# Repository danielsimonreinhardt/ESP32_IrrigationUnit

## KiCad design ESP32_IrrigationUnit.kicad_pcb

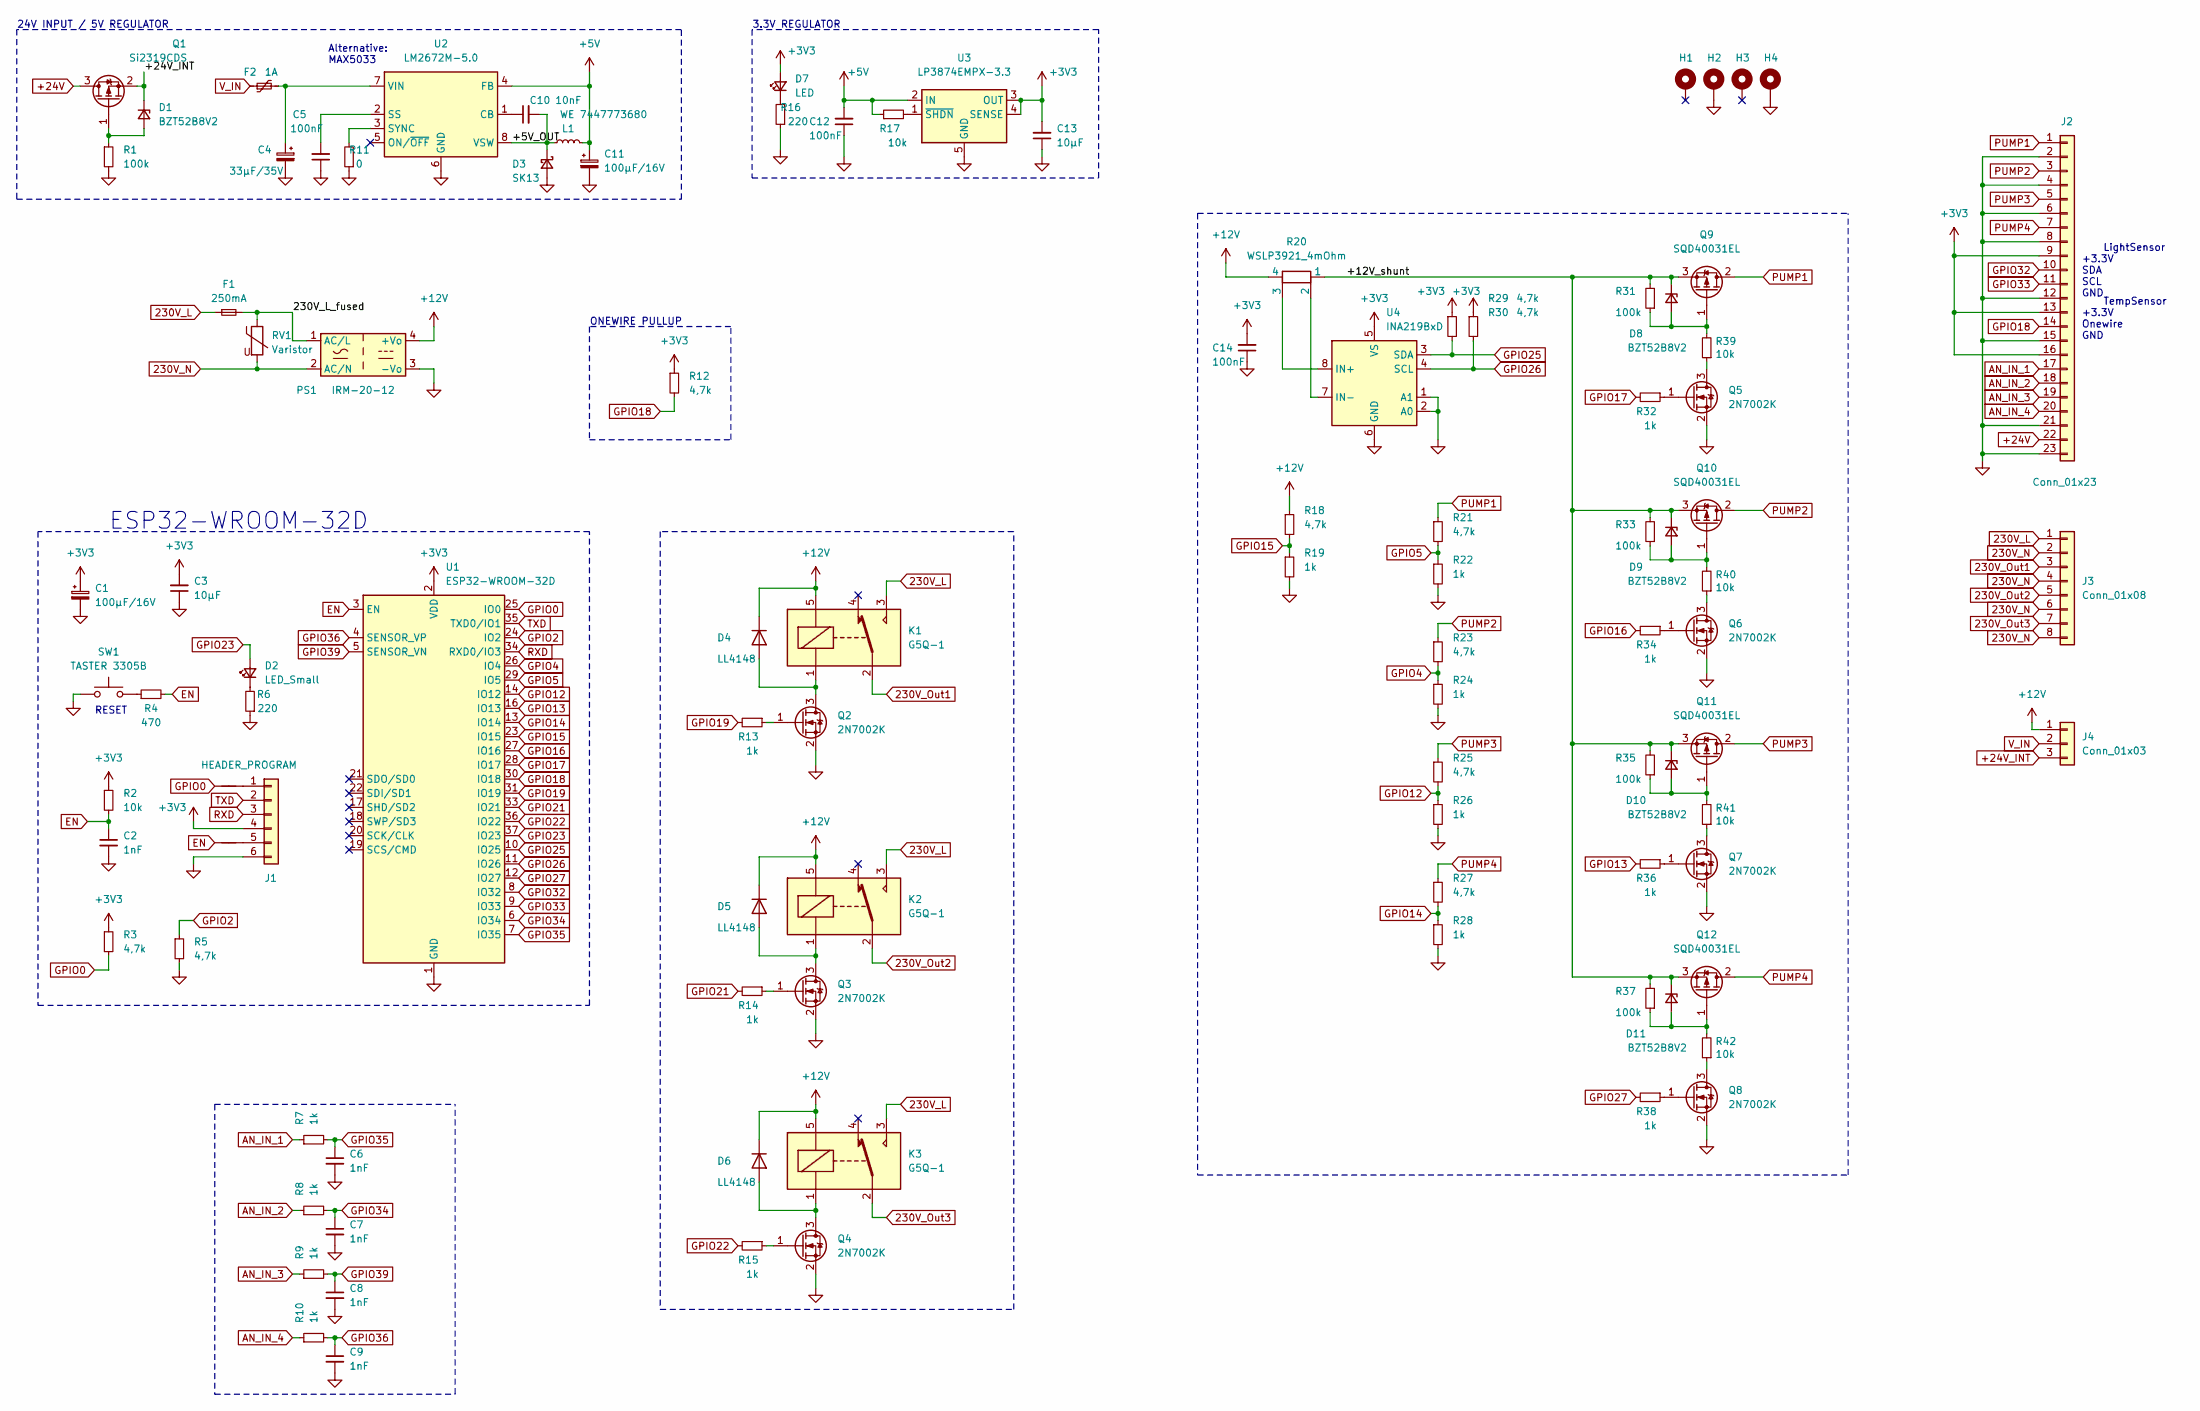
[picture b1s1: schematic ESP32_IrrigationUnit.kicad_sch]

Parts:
C1, C11: 100µF/16V; CP_Elec_6.3x5.8
C2, C6, C7, C8, C9: 1nF; C_0603_1608Metric
C3, C13: 10µF; C_0805_2012Metric
C4: 33µF/35V; CP_Elec_6.3x5.8
C5, C12, C14: 100nF; C_0603_1608Metric
C10: 10nF; C_0603_1608Metric
D1, D8, D9, D10, D11: BZT52B8V2; D_SOD-123
D2: LED_Small; LED_D3.0mm_Horizontal_O3.81mm_Z6.0mm
D3: SK13; D_SMB
D4, D5, D6: LL4148; D_MiniMELF
D7: LED; LED_D3.0mm_Horizontal_O3.81mm_Z6.0mm
F1: 250mA; Fuseholder_Cylinder-5x20mm_Schurter_OGN-SMD_Horizontal_Open
F2: 1A; Fuse_1206_3216Metric
H1, H2, H3, H4: MountingHole_Pad; MountingHole_4.3mm_M4_ISO14580_Pad_TopBottom
J1: HEADER_PROGRAM; PinHeader_1x06_P2.54mm_Vertical
J2: Conn_01x23; TE_AMPSEAL_1-776087-x_3Rows_23_P0.4mm_Horizontal
J3: Conn_01x08; TE_AMPSEAL_1-776280-1
J4: Conn_01x03; SolderJumper-3_P2.0mm_Open_TrianglePad1.0x1.5mm
K1, K2, K3: G5Q-1; Relay_SPDT_Omron-G5Q-1
L1: WE 7447773680; L_Wuerth_WE-PD-Typ-7345
NT1, NT2: NetTie_2; SolderJumper-2_P1.3mm_Open_TrianglePad1.0x1.5mm
PS1: IRM-20-12; Converter_ACDC_MeanWell_IRM-20-xx_THT
Q1: Si2319CDS; SOT-23
Q2, Q3, Q4, Q5, Q6, Q7, Q8: 2N7002K; SOT-23
Q9, Q10, Q11, Q12: SQD40031EL; TO-252-2
R1, R31, R33, R35, R37: 100k; R_0603_1608Metric
R2, R17, R39, R40, R41, R42: 10k; R_0603_1608Metric
R3, R5, R12, R18, R21, R23, R25, R27, R29, R30: 4,7k; R_0603_1608Metric
R4: 470; R_0603_1608Metric
R6, R16: 220; R_0603_1608Metric
R7, R8, R9, R10, R13, R14, R15, R19, R22, R24, R26, R28, R32, R34, R36, R38: 1k; R_0603_1608Metric
R11: 0; R_0603_1608Metric
R20: WSLP3921_4mOhm; R_Shunt_Vishay_WSLP3921
RV1: Varistor; RV_Disc_D7mm_W3.4mm_P5mm
SW1: TASTER 3305B; SW_Tactile_SPST_Angled_PTS645Vx83-2LFS
U1: ESP32-WROOM-32D; ESP32-WROOM-32U
U2: LM2672M-5.0; SOIC-8_3.9x4.9mm_P1.27mm
U3: LP3874EMPX-3.3; SOT-223-5
U4: INA219BxD; SOIC-8_3.9x4.9mm_P1.27mm

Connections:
230V_L: F1.1, J3.1, K1.3, K2.3, K3.3
230V_N: J3.2, J3.4, J3.6, J3.8, PS1.2 (AC/N), RV1.2
230V_Out1: J3.3, K1.2
230V_Out2: J3.5, K2.2
230V_Out3: J3.7, K3.2
+3V3: C1.1, C3.2, C13.2, C14.2, D7.2 (A), J1.4, J2.9, J2.13, J2.16, R2.1, R3.1, R12.1, R29.1, R30.1, U1.2 (VDD), U3.3 (OUT), U3.4 (SENSE), U4.5 (VS)
+5V: C11.1, C12.2, L1.2, R17.1, U2.4 (FB), U3.2 (IN)
+12V: D4.1 (K), D5.1 (K), D6.1 (K), J4.1, K1.5, K2.5, K3.5, PS1.4 (+Vo), R18.1, R20.4
+24V: J2.22, Q1.3 (D)
+24V_INT: D1.1 (K), J4.3, Q1.2 (S)
/230V_L_fused: F1.2, PS1.1 (AC/L), RV1.1
/+5V_OUT: C10.2, D3.1 (K), L1.1, U2.8 (VSW)
/+12V_shunt: D8.1 (K), D9.1 (K), D10.1 (K), D11.1 (K), Q9.3 (S), Q10.3 (S), Q11.3 (S), Q12.3 (S), R20.1, R31.2, R33.2, R35.2, R37.2
AN_IN_1: J2.17, R7.1
AN_IN_2: J2.18, R8.1
AN_IN_3: J2.19, R9.1
AN_IN_4: J2.20, R10.1
EN: C2.1, NT2.1, R2.2, R4.2, U1.3 (EN)
GND: C1.2, C2.2, C3.1, C4.2, C5.1, C6.2, C7.2, C8.2, C9.2, C11.2, C12.1, C13.1, C14.1, D3.2 (A), H2.1, H4.1, J1.6, J2.2, J2.4, J2.6, J2.8, J2.12, J2.15, J2.21, J2.23, PS1.3 (-Vo), Q2.2 (S), Q3.2 (S), Q4.2 (S), Q5.2 (S), Q6.2 (S), Q7.2 (S), Q8.2 (S), R1.2, R5.2, R6.1, R11.1, R16.1, R19.2, R22.2, R24.2, R26.2, R28.2, SW1.1, U1.1 (GND), U1.15 (GND), U1.38 (GND), U1.39 (GND), U2.6 (GND), U3.5 (GND), U4.1 (A1), U4.2 (A0), U4.6 (GND)
GPIO0: NT1.1, R3.2, U1.25 (IO0)
GPIO2: R5.1, U1.24 (IO2)
GPIO4: R23.2, R24.1, U1.26 (IO4)
GPIO5: R21.2, R22.1, U1.29 (IO5)
GPIO12: R25.2, R26.1, U1.14 (IO12)
GPIO13: R36.2, U1.16 (IO13)
GPIO14: R27.2, R28.1, U1.13 (IO14)
GPIO15: R18.2, R19.1, U1.23 (IO15)
GPIO16: R34.2, U1.27 (IO16)
GPIO17: R32.2, U1.28 (IO17)
GPIO18: J2.14, R12.2, U1.30 (IO18)
GPIO19: R13.2, U1.31 (IO19)
GPIO21: R14.2, U1.33 (IO21)
GPIO22: R15.2, U1.36 (IO22)
GPIO23: D2.2 (A), U1.37 (IO23)
GPIO25: R29.2, U1.10 (IO25), U4.3 (SDA)
GPIO26: R30.2, U1.11 (IO26), U4.4 (SCL)
GPIO27: R38.2, U1.12 (IO27)
GPIO32: J2.10, U1.8 (IO32)
GPIO33: J2.11, U1.9 (IO33)
GPIO34: C7.1, R8.2, U1.6 (IO34)
GPIO35: C6.1, R7.2, U1.7 (IO35)
GPIO36: C9.1, R10.2, U1.4 (SENSOR_VP)
GPIO39: C8.1, R9.2, U1.5 (SENSOR_VN)
unnamed: C4.1, F2.2, U2.7 (VIN)
unnamed: C5.2, U2.2 (SS)
unnamed: C10.1, U2.1 (CB)
unnamed: D1.2 (A), Q1.1 (G), R1.1
unnamed: D2.1 (K), R6.2
unnamed: D4.2 (A), K1.1, Q2.3 (D)
unnamed: D5.2 (A), K2.1, Q3.3 (D)
unnamed: D6.2 (A), K3.1, Q4.3 (D)
unnamed: D7.1 (K), R16.2
unnamed: D8.2 (A), Q9.1 (G), R31.1, R39.2
unnamed: D9.2 (A), Q10.1 (G), R33.1, R40.2
unnamed: D10.2 (A), Q11.1 (G), R35.1, R41.2
unnamed: D11.2 (A), Q12.1 (G), R37.1, R42.2
unnamed: J1.1, NT1.2
unnamed: J1.5, NT2.2
unnamed: Q2.1 (G), R13.1
unnamed: Q3.1 (G), R14.1
unnamed: Q4.1 (G), R15.1
unnamed: Q5.1 (G), R32.1
unnamed: Q5.3 (D), R39.1
unnamed: Q6.1 (G), R34.1
unnamed: Q6.3 (D), R40.1
unnamed: Q7.1 (G), R36.1
unnamed: Q7.3 (D), R41.1
unnamed: Q8.1 (G), R38.1
unnamed: Q8.3 (D), R42.1
unnamed: R4.1, SW1.2
unnamed: R11.2, U2.3 (SYNC)
unnamed: R17.2, U3.1 (~SHDN)
unnamed: R20.2, U4.7 (IN-)
unnamed: R20.3, U4.8 (IN+)
PUMP1: J2.1, Q9.2 (D), R21.1
PUMP2: J2.3, Q10.2 (D), R23.1
PUMP3: J2.5, Q11.2 (D), R25.1
PUMP4: J2.7, Q12.2 (D), R27.1
RXD: J1.3, U1.34 (RXD0/IO3)
TXD: J1.2, U1.35 (TXD0/IO1)
V_IN: F2.1, J4.2

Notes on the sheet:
RESET
24V INPUT / 5V REGULATOR
ESP32-WROOM-32D
TempSensor +3.3V Onewire GND
Alternative: MAX5033
ONEWIRE PULLUP
LightSensor +3.3V SDA SCL GND
3.3V REGULATOR

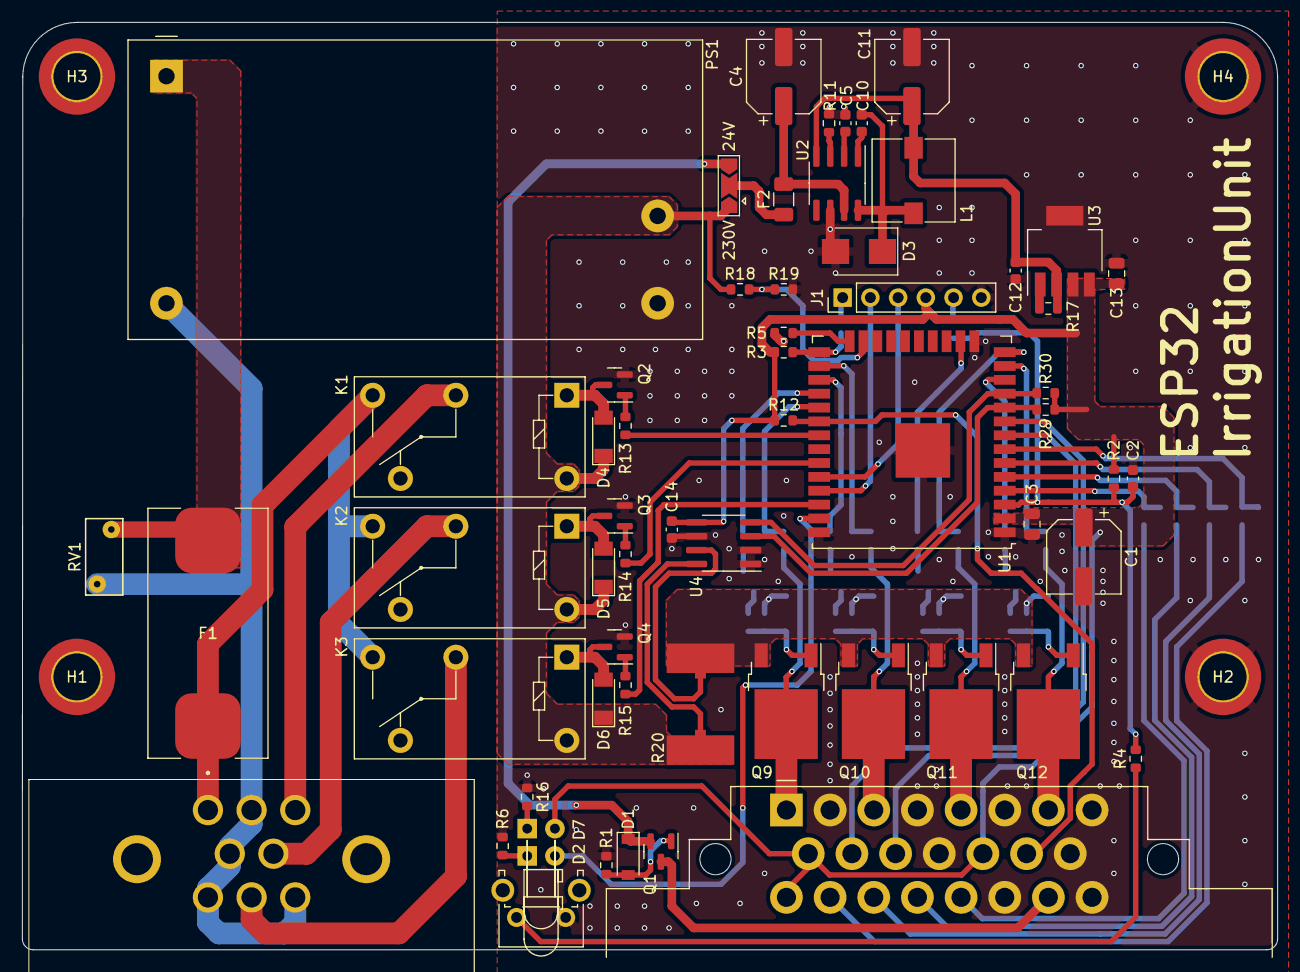
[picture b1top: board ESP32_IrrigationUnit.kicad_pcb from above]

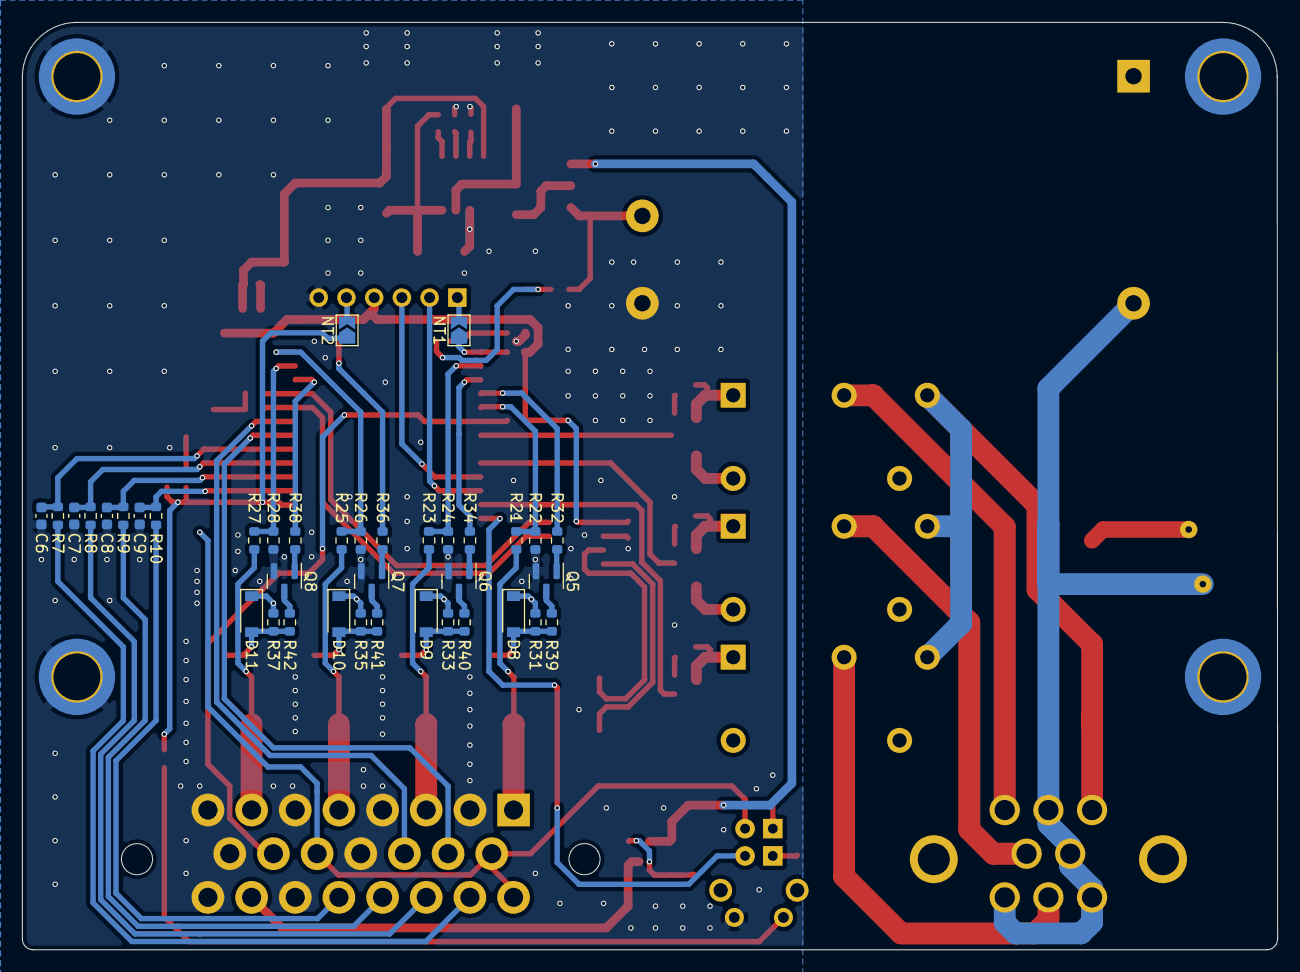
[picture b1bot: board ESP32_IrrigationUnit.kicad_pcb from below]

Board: 2 copper layers, 115.0 x 85.0 mm, 102 parts (38 on the bottom side), 81 nets.
